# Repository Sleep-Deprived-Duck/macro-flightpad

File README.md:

# macro-flightpad

The Flightpad is a simple 4-key macropad with a rotary encoder mostly intended for playing the occasional flight sim without a HOTAS.

Features:
4 Cherry-MX style keys
1 rotary encoder (I'll be using it for things like roll controls on old emulated console games but you can do whatever you want)

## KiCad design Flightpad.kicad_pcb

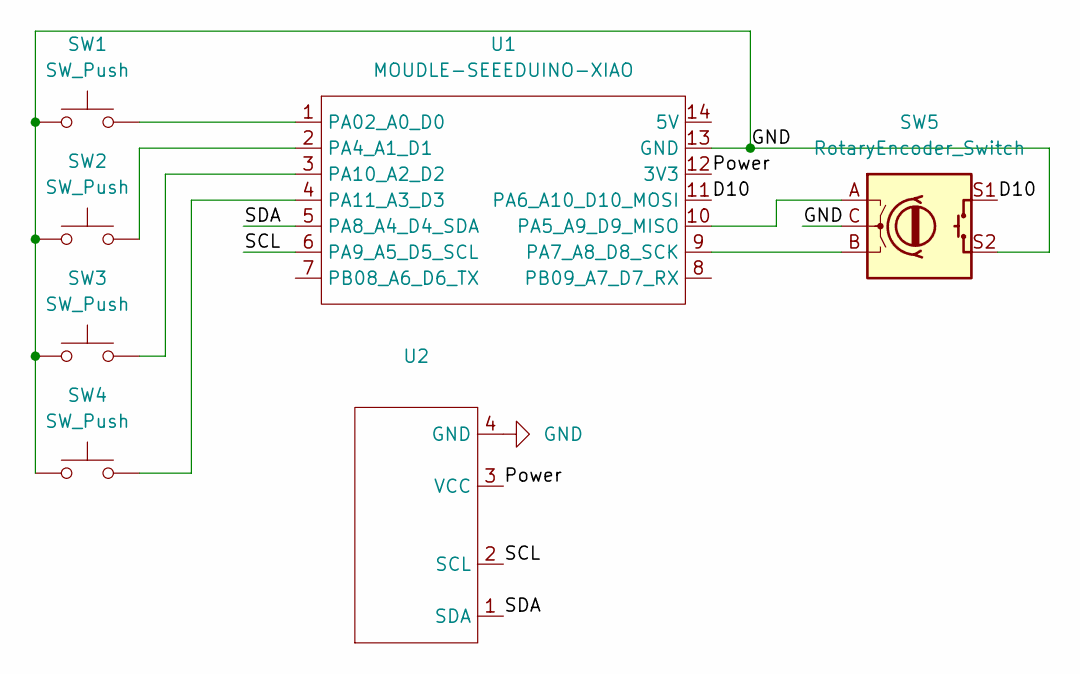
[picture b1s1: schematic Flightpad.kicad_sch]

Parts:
SW1, SW2, SW3, SW4: SW_Push; SW_Cherry_MX_1.00u_PCB
SW5: RotaryEncoder_Switch; RotaryEncoder_Alps_EC11E-Switch_Vertical_H20mm
U1: MOUDLE-SEEEDUINO-XIAO; XIAO-Generic-Hybrid-14P-2.54-21X17.8MM
U2: FanPinHeader_1x04_P2.54mm_Vertical

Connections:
/D10: SW5.S1, U1.11 (PA6_A10_D10_MOSI)
/Power: U1.12 (3V3), U2.3 (VCC)
/SCL: U1.6 (PA9_A5_D5_SCL), U2.2 (SCL)
/SDA: U1.5 (PA8_A4_D4_SDA), U2.1 (SDA)
GND: SW1.1, SW2.1, SW3.1, SW4.1, SW5.C, SW5.S2, U1.13 (GND), U2.4 (GND)
unnamed: SW1.2, U1.1 (PA02_A0_D0)
unnamed: SW2.2, U1.2 (PA4_A1_D1)
unnamed: SW5.A, U1.10 (PA5_A9_D9_MISO)
unnamed: SW5.B, U1.9 (PA7_A8_D8_SCK)
unnamed: SW3.2, U1.3 (PA10_A2_D2)
unnamed: SW4.2, U1.4 (PA11_A3_D3)

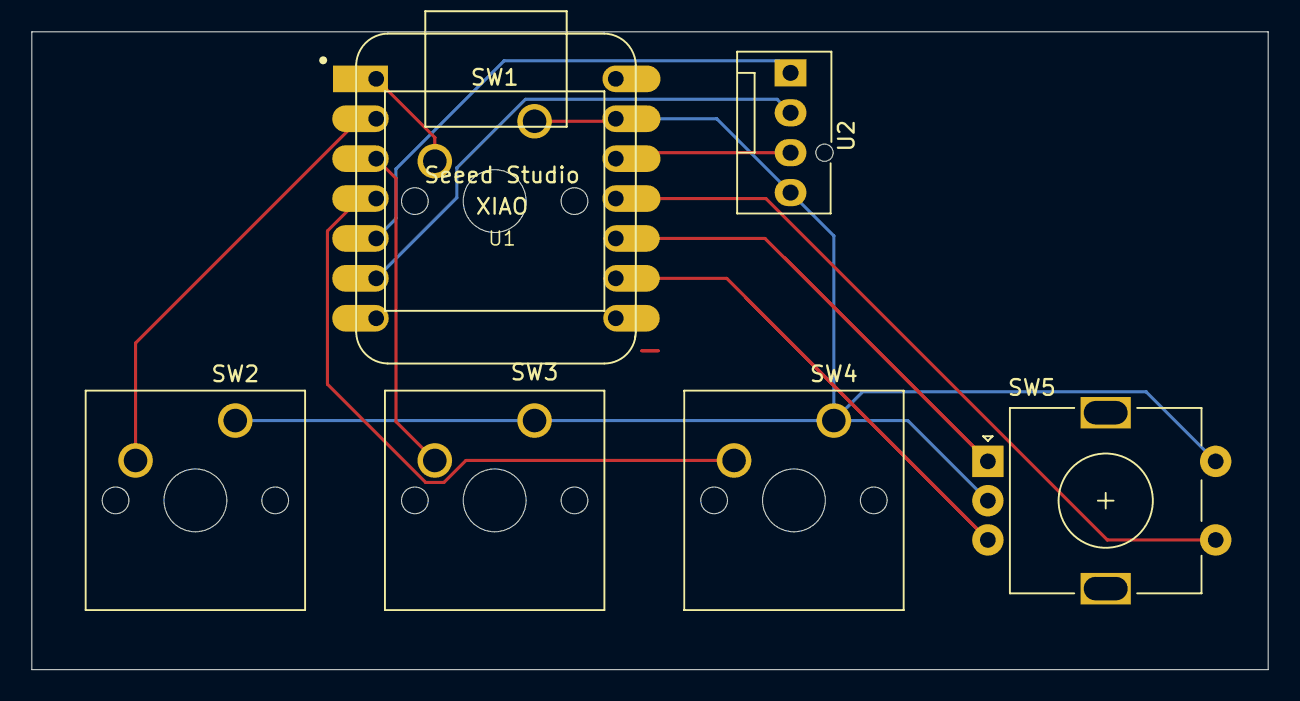
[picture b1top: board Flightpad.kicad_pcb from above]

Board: 2 copper layers, 78.7 x 40.6 mm, 7 parts (0 on the bottom side), 11 nets.
